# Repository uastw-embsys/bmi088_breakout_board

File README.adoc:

== DrohnFH BMI088 Breakout Board

This breakout board connects all the pins of the BMI088 IMU Sensor IC
to a DIP-16 footprint.

[frame="none",grid="none",cols="^.^4,^.^9,width="100%"]
|====
| image:docs/bmi088_breakout.png[] | image:docs/bmi088_breakout.jpg[]
|====

WARNING: To keep routing as simple as possible, it does *not* follow the
conventional DIP pin assignment! Please use the connection diagrams below
to connect the breakout board correctly.

The breakout board's pin assignment can be found in its link:datasheet/datasheet.pdf[Datasheet].

It is pin-compatible with the link:https://github.com/uastw-embsys/icm42688_breakout_board[ICM42688 Breakout Board] for both SPI and I2C.

For further details see the sensor's datasheet (https://www.bosch-sensortec.com/media/boschsensortec/downloads/datasheets/bst-bmi088-ds001.pdf)

=== Revision 2

Revision 2 adds silkscreen markings for the individual pins.
It is electrically otherwise unchanged.

=== Hints

* VDDIO range: 1.2 -- 3.6 V
* VDD range: 2.4 -- 3.6 V

* From the datasheet (pg. 34): "The interface of the gyroscope part is selected by the level of the PS pin. In contrast to this, the accelerometer part starts always in I2C mode
(regardless of the level of the PS pin) and needs to be changed to SPI mode actively by sending
a rising edge on the `CSB1` pin (chip select of the accelerometer), on which the accelerometer
part switches to SPI mode and stays in this mode until the next power-up-reset.
To change the sensor to SPI mode in the initialization phase, the user could perfom a dummy
SPI read operation, e.g. of register `ACC_CHIP_ID` (the obtained value will be invalid)."

For further details see the datasheet (https://www.bosch-sensortec.com/media/boschsensortec/downloads/datasheets/bst-bmi088-ds001.pdf)

=== Acknowledgement

This work was supported by the City of Vienna via the project 
_Stadt Wien Kompetenzteam für Drohnentechnik in der Fachhochschulausbildung_,
MA23 Projekt Nr. 35-02.

[grid="none",frame="none"]
|====
| image:docs/drohnfh_logo_80.png[] | image:docs/ma23_80.png[] | image:docs/fhtw_80.png[]
|====

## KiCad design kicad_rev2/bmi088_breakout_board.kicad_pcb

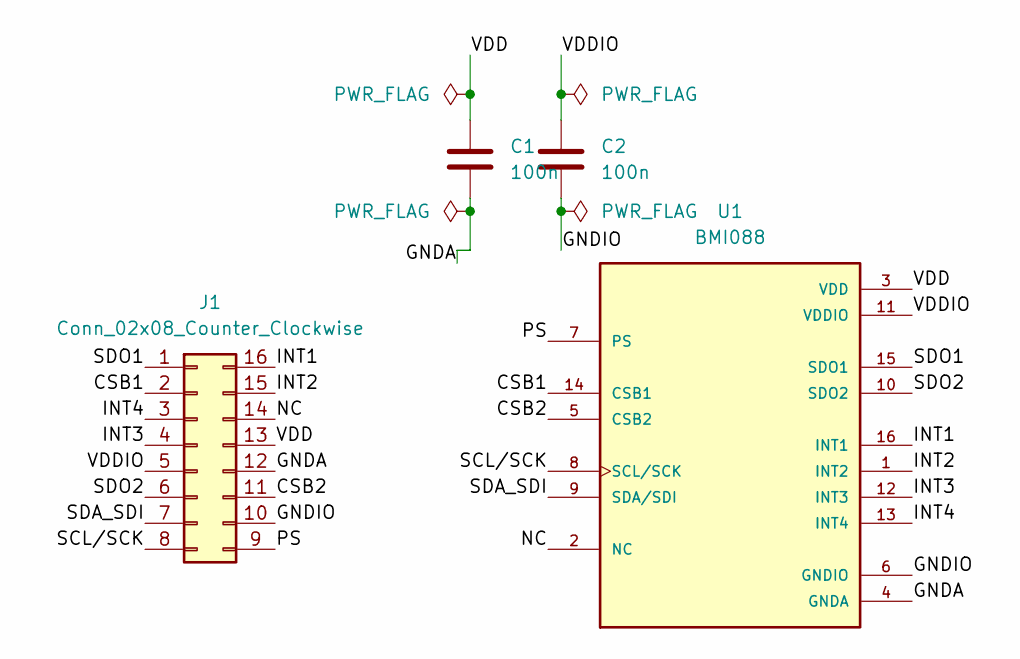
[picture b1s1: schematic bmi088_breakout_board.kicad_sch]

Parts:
C1, C2: 100n; C_0603_1608Metric
J1: Conn_02x08_Counter_Clockwise; castello
U1: BMI088; PQFN50P450X300X100-16N

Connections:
/CSB1: J1.2, U1.14 (CSB1)
/CSB2: J1.11, U1.5 (CSB2)
/GNDA: C1.2, J1.12, U1.4 (GNDA)
/GNDIO: C2.2, J1.10, U1.6 (GNDIO)
/INT1: J1.16, U1.16 (INT1)
/INT2: J1.15, U1.1 (INT2)
/INT3: J1.4, U1.12 (INT3)
/INT4: J1.3, U1.13 (INT4)
/NC: J1.14, U1.2 (NC)
/PS: J1.9, U1.7 (PS)
/SCL/SCK: J1.8, U1.8 (SCL/SCK)
/SDA_SDI: J1.7, U1.9 (SDA/SDI)
/SDO1: J1.1, U1.15 (SDO1)
/SDO2: J1.6, U1.10 (SDO2)
/VDD: C1.1, J1.13, U1.3 (VDD)
/VDDIO: C2.1, J1.5, U1.11 (VDDIO)

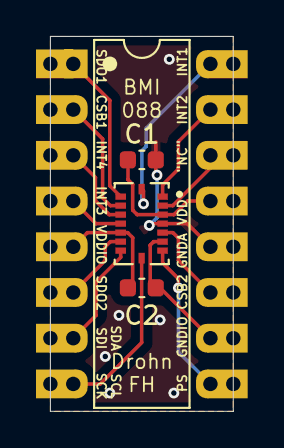
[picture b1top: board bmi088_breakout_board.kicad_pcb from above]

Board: 2 copper layers, 10.2 x 20.8 mm, 4 parts (0 on the bottom side), 16 nets.

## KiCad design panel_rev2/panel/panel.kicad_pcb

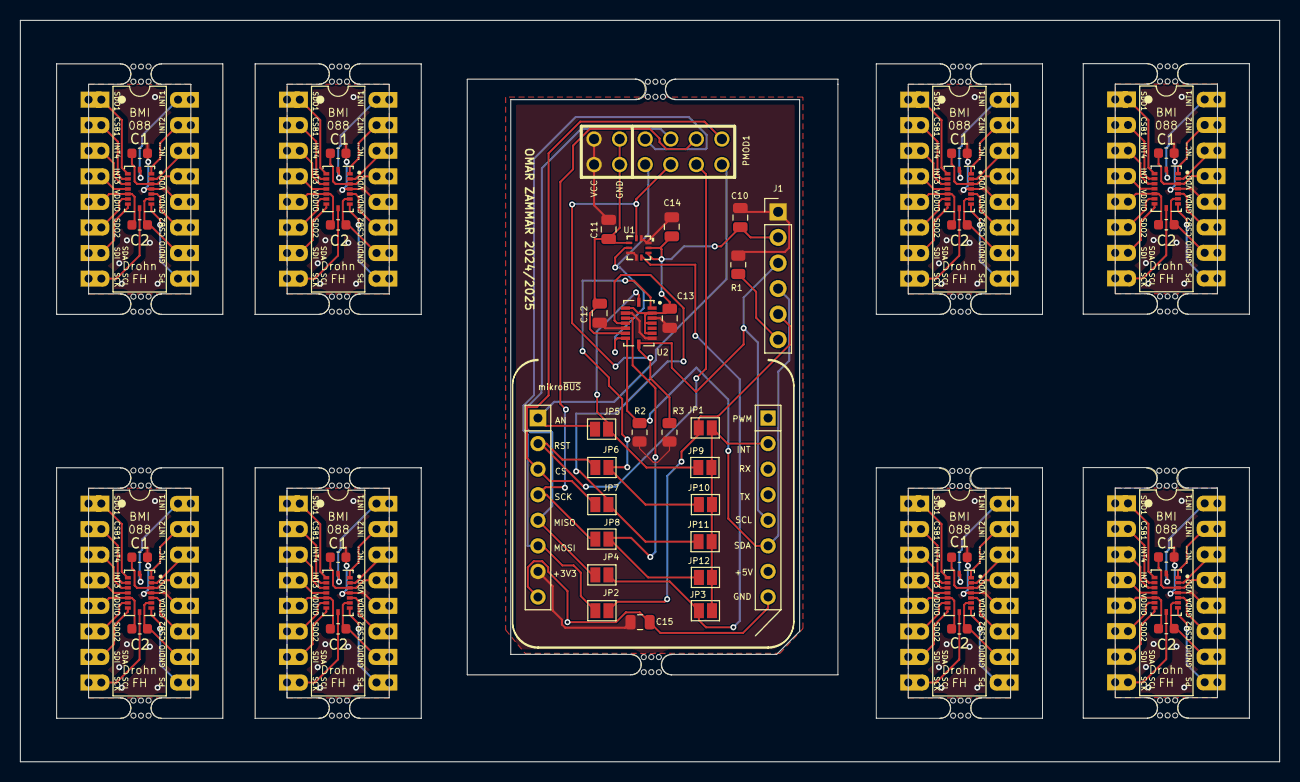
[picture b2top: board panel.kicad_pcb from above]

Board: 2 copper layers, 125.1 x 73.7 mm, 76 parts (0 on the bottom side), 34 nets.

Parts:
C1, C2, C3, C4, C5, C6, C7, C8, C9, C21, C22, C23, C24, C25, C26, C27: 100n; C_0603_1608Metric
C10, C11, C12, C13, C14, C15: 100n; C_0805_2012Metric
CON1: MIKROBUS_HOST_CONN_IN_GND; MIKROBUS_HOST_CONN
J1: Conn_01x06; PinHeader_1x06_P2.54mm_Vertical
J1#2, J2, J3, J4, J5, J6, J7, J8: Conn_02x08_Counter_Clockwise; castello
JP1, JP2, JP3, JP4, JP5, JP6, JP7, JP8, JP9, JP10, JP11, JP12: SolderJumper_2_Open; SolderJumper-2_P1.3mm_Open_Pad1.0x1.5mm
PMOD1: PMOD-Device-x2-Type-1A-GPIO_1; pmod_pin_array_6x2
R1, R2, R3: 4.7k; R_0805_2012Metric
U1: BMP390; 10LGA_2X2X0p75_BOS
U2, U3, U4, U5, U6, U7, U8, U9, U10: BMI088; PQFN50P450X300X100-16N
mouse-bite-2mm-slot, mouse-bite-2mm-slot#2, mouse-bite-2mm-slot#3, mouse-bite-2mm-slot#4, mouse-bite-2mm-slot#5, mouse-bite-2mm-slot#6, mouse-bite-2mm-slot#7, mouse-bite-2mm-slot#8, mouse-bite-2mm-slot#9, mouse-bite-2mm-slot#10, mouse-bite-2mm-slot#11, mouse-bite-2mm-slot#12, mouse-bite-2mm-slot#13, mouse-bite-2mm-slot#14, mouse-bite-2mm-slot#15, mouse-bite-2mm-slot#16, mouse-bite-2mm-slot#17, mouse-bite-2mm-slot#18: VAL**; mouse-bite-2mm-slot

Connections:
/3V3: C10.1, C11.1, C12.1, C13.1, C14.1, C15.1, CON1.P7 (3V3), J1.1, PMOD1.6 (VCC), PMOD1.12 (VCC), R1.2, R2.1, R3.1, U1.1 (VDDIO), U1.5 (SDO), U1.6 (CSB), U1.10 (VDD), U2.3 (VDD), U2.7 (PS), U2.11 (VDDIO), U2.14 (CSB1)
/BARO_INT: CON1.P5 (MISO), JP4.2 (B), PMOD1.9 (IOB2)
/CSB1: J1#2.2, J2.2, J3.2, J4.2, J5.2, J6.2, J7.2, J8.2, U3.14 (CSB1), U4.14 (CSB1), U5.14 (CSB1), U6.14 (CSB1), U7.14 (CSB1), U8.14 (CSB1), U9.14 (CSB1), U10.14 (CSB1)
/CSB2: J1#2.11, J2.11, J3.11, J4.11, J5.11, J6.11, J7.11, J8.11, U3.5 (CSB2), U4.5 (CSB2), U5.5 (CSB2), U6.5 (CSB2), U7.5 (CSB2), U8.5 (CSB2), U9.5 (CSB2), U10.5 (CSB2)
/DIST_INT: CON1.P6 (MOSI), JP2.1 (A), PMOD1.10 (IOB3)
/GNDA: C1.2, C3.2, C4.2, C5.2, C6.2, C7.2, C8.2, C9.2, J1#2.12, J2.12, J3.12, J4.12, J5.12, J6.12, J7.12, J8.12, U3.4 (GNDA), U4.4 (GNDA), U5.4 (GNDA), U6.4 (GNDA), U7.4 (GNDA), U8.4 (GNDA), U9.4 (GNDA), U10.4 (GNDA)
/GNDIO: C2.2, C21.2, C22.2, C23.2, C24.2, C25.2, C26.2, C27.2, J1#2.10, J2.10, J3.10, J4.10, J5.10, J6.10, J7.10, J8.10, U3.6 (GNDIO), U4.6 (GNDIO), U5.6 (GNDIO), U6.6 (GNDIO), U7.6 (GNDIO), U8.6 (GNDIO), U9.6 (GNDIO), U10.6 (GNDIO)
/IMU_INT 1: CON1.P1 (AN), JP5.2 (B), PMOD1.1 (IOA0)
/IMU_INT 2: CON1.P2 (RST), JP6.2 (B), PMOD1.2 (IOA1)
/IMU_INT 3: CON1.P3 (CS), JP7.2 (B), PMOD1.7 (IOB0)
/IMU_INT 4: CON1.P4 (SCK), JP8.2 (B), PMOD1.8 (IOB1)
/INT: CON1.P15 (INT), JP1.2 (B), JP3.2 (B), JP9.2 (B), JP10.2 (B), JP11.2 (B), JP12.2 (B)
/INT1: J1#2.16, J2.16, J3.16, J4.16, J5.16, J6.16, J7.16, J8.16, U3.16 (INT1), U4.16 (INT1), U5.16 (INT1), U6.16 (INT1), U7.16 (INT1), U8.16 (INT1), U9.16 (INT1), U10.16 (INT1)
/INT2: J1#2.15, J2.15, J3.15, J4.15, J5.15, J6.15, J7.15, J8.15, U3.1 (INT2), U4.1 (INT2), U5.1 (INT2), U6.1 (INT2), U7.1 (INT2), U8.1 (INT2), U9.1 (INT2), U10.1 (INT2)
/INT3: J1#2.4, J2.4, J3.4, J4.4, J5.4, J6.4, J7.4, J8.4, U3.12 (INT3), U4.12 (INT3), U5.12 (INT3), U6.12 (INT3), U7.12 (INT3), U8.12 (INT3), U9.12 (INT3), U10.12 (INT3)
/INT4: J1#2.3, J2.3, J3.3, J4.3, J5.3, J6.3, J7.3, J8.3, U3.13 (INT4), U4.13 (INT4), U5.13 (INT4), U6.13 (INT4), U7.13 (INT4), U8.13 (INT4), U9.13 (INT4), U10.13 (INT4)
/NC: J1#2.14, J2.14, J3.14, J4.14, J5.14, J6.14, J7.14, J8.14, U3.2 (NC), U4.2 (NC), U5.2 (NC), U6.2 (NC), U7.2 (NC), U8.2 (NC), U9.2 (NC), U10.2 (NC)
/PS: J1#2.9, J2.9, J3.9, J4.9, J5.9, J6.9, J7.9, J8.9, U3.7 (PS), U4.7 (PS), U5.7 (PS), U6.7 (PS), U7.7 (PS), U8.7 (PS), U9.7 (PS), U10.7 (PS)
/SCL: CON1.P12 (SCL), J1.3, PMOD1.3 (IOA2), R3.2, U1.2 (SCK), U2.8 (SCL/SCK)
/SCL/SCK: J1#2.8, J2.8, J3.8, J4.8, J5.8, J6.8, J7.8, J8.8, U3.8 (SCL/SCK), U4.8 (SCL/SCK), U5.8 (SCL/SCK), U6.8 (SCL/SCK), U7.8 (SCL/SCK), U8.8 (SCL/SCK), U9.8 (SCL/SCK), U10.8 (SCL/SCK)
/SDA: CON1.P11 (SDA), J1.4, PMOD1.4 (IOA3), R2.2, U1.4 (SDI), U2.9 (SDA/SDI)
/SDA_SDI: J1#2.7, J2.7, J3.7, J4.7, J5.7, J6.7, J7.7, J8.7, U3.9 (SDA/SDI), U4.9 (SDA/SDI), U5.9 (SDA/SDI), U6.9 (SDA/SDI), U7.9 (SDA/SDI), U8.9 (SDA/SDI), U9.9 (SDA/SDI), U10.9 (SDA/SDI)
/SDO1: J1#2.1, J2.1, J3.1, J4.1, J5.1, J6.1, J7.1, J8.1, U3.15 (SDO1), U4.15 (SDO1), U5.15 (SDO1), U6.15 (SDO1), U7.15 (SDO1), U8.15 (SDO1), U9.15 (SDO1), U10.15 (SDO1)
/SDO2: J1#2.6, J2.6, J3.6, J4.6, J5.6, J6.6, J7.6, J8.6, U3.10 (SDO2), U4.10 (SDO2), U5.10 (SDO2), U6.10 (SDO2), U7.10 (SDO2), U8.10 (SDO2), U9.10 (SDO2), U10.10 (SDO2)
/VDD: C1.1, C3.1, C4.1, C5.1, C6.1, C7.1, C8.1, C9.1, J1#2.13, J2.13, J3.13, J4.13, J5.13, J6.13, J7.13, J8.13, U3.3 (VDD), U4.3 (VDD), U5.3 (VDD), U6.3 (VDD), U7.3 (VDD), U8.3 (VDD), U9.3 (VDD), U10.3 (VDD)
/VDDIO: C2.1, C21.1, C22.1, C23.1, C24.1, C25.1, C26.1, C27.1, J1#2.5, J2.5, J3.5, J4.5, J5.5, J6.5, J7.5, J8.5, U3.11 (VDDIO), U4.11 (VDDIO), U5.11 (VDDIO), U6.11 (VDDIO), U7.11 (VDDIO), U8.11 (VDDIO), U9.11 (VDDIO), U10.11 (VDDIO)
GND: C10.2, C11.2, C12.2, C13.2, C14.2, C15.2, CON1.P8 (GND1), CON1.P9 (GND2), J1.2, PMOD1.5 (GND), PMOD1.11 (GND), U1.3 (VSS), U1.8 (VSS), U1.9 (VSS), U2.2 (NC), U2.4 (GNDA), U2.6 (GNDIO), U2.10 (SDO2), U2.15 (SDO1)
unnamed: J1.5, JP1.1 (A), JP2.2 (B)
unnamed: J1.6, R1.1
unnamed: JP3.1 (A), JP4.1 (A), U1.7 (INT)
unnamed: JP5.1 (A), JP9.1 (A), U2.16 (INT1)
unnamed: JP6.1 (A), JP10.1 (A), U2.1 (INT2)
unnamed: JP7.1 (A), JP11.1 (A), U2.12 (INT3)
unnamed: JP8.1 (A), JP12.1 (A), U2.13 (INT4)

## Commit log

2025-01-29 Initial
2025-01-29 add docs
2025-01-29 Update docs
2025-02-18 Refine Docs
2025-02-21 Refine hello world software
2025-02-21 Legal
2025-03-19 Add SPI example
2025-03-19 Fix header
2026-04-08 Add Rev2
2026-06-12 add datasheet
2026-06-19 Add LICENSE
2026-06-19 add datasheet pdf
